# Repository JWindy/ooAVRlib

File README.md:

# ooAVRlib - object oriented AVR library
I started my first embedded projects with Arduino. Due to high power consumption for battery powered projects and relatively large size for projects in confined space, I moved to ATMEL AVR microcontrollers. Mostly, I use ATtiny 85. Since I'm a fan of object oriented programming and I loved the Arduino framework with all the libraries, I started implementing libraries to make life easier. The goal of the libraries is to provide basics functions, to speed up the implementation of new projects. By breaking the functionality down in encapsulated modules, I can reduce complexity for debugging. In case an application source code should get to big, I still can copy the required lines of code together and should have much less troubble interpreting the data sheet and searching for bugs, compared to implementing everything from scratch.
With this repository, I intent to share the libraries to anyone interested and provide some material for beginners, who hopefully have an easier start with my rather simple libraries. It would also be great to find someone willing to contribute to the libraries or get some feedback from more experienced developers. I'm neither a professional software nor hardware engineer;)

# Work in progress
I'm currently working on the initial implementation of the libraries. As soon as the first libraries are tested and ready for use, I'll upload a release.

# How to use the libraries
For every library, you'll find the following folders:
- assets -> any further information like class or block diagrams, if relevant.
- hardware -> This folder contains the design of the hardware used for testing the library. For basic libraries, I'll use a debugging board solderd on a prototype board, which you can find in the folder "debugging boards".
- lib -> If other libraries are required for running the library, the corresponding files are copied here.
- libXX.cpp -> source file
- libXX.h -> header file
- libXXTest.cpp -> test file. The test file shows how to use each function, together with the information in the hardware folder, this should be sufficient documentation to get started:D

# Microcontrollers
For now, the libraries will be implemented for ATtiny 85 running at 8 MHz. I plan on supporting other clock frequencies as well as ATtiny 84 and ATmega 328 in the future.

# Toolchain
I published the project files of the schematics and layouts as well as of the IDE. If you encounter any problems, it might help, to try to open the projects as they are and search for the difference. 
- coding: MPLAB® X IDE -> https://www.microchip.com/en-us/tools-resources/develop/mplab-x-ide
- additional compiler flags: -std=c++14
- programming and debugging: ATMEL-ICE -> https://www.microchip.com/en-us/development-tool/atatmel-ice
- schematics and layouts: KiCad -> https://www.kicad.org/

# Overview over the libraries
The libraries can be grouped in hardware proxies, general purpose libraries, development tools and application level. 
In general, you find more information in the header file of each library, which I don't want to copy here;)
## Hardware Proxies/Drivers
These libraries give access to microcontroller capabilites on the lowest level. Since the ressource can only be accessed by one user, most of the libraries are implemented as singleton and protected by a semaphore.
### libIOHandler
libIOHandler provides basic functions to set a pin as output or input, to activate the internal pullup for input pins, to set a pin high or low and to read the state of a input pin.
### libTimer
This library implements the capabilities of the timer0 and timer1. The timer can be used to trigger interrputs (CTC mode) or to output a PWM signal (PWM mode). 
## General purpose libraries
### libUtility
libUtility contains general type definitions, which will be used to implement the interfaces between libraries. Furthermore, a semaphore is implemented to provide locking functionality especially to hardware proxies to avoide multiple access. This feature might be overengineered for hobby applications, but it was fun to understand, how a semaphore works;)
## Development tools
Development tools are usefull for debugging and testing of other libraries and application code. This group will cover functionality implementing the interface to the serial montior and logging and error handling. The libraries might also be usefull on application level, but so far, I always deactivated these functions, when finishing the project.
### libUartTx
This library provides functions to send strings and numbers (uint and int, 8- and 16-bit) to a serial monitor. To access the UART interface, a USB-UART-adapter is required. I use this function primarily for debugging and logging. libUartTx implements the UART protocol in SW and can be hooked up on any GPIO pin. The library is implemented as singleton, but not protected. So any user can send data. The CPU cycle is blocked until all data is send, so users can access the transmitting function in serial. 
## Application level
So far, I'm still ocupied with the basic libraries;)

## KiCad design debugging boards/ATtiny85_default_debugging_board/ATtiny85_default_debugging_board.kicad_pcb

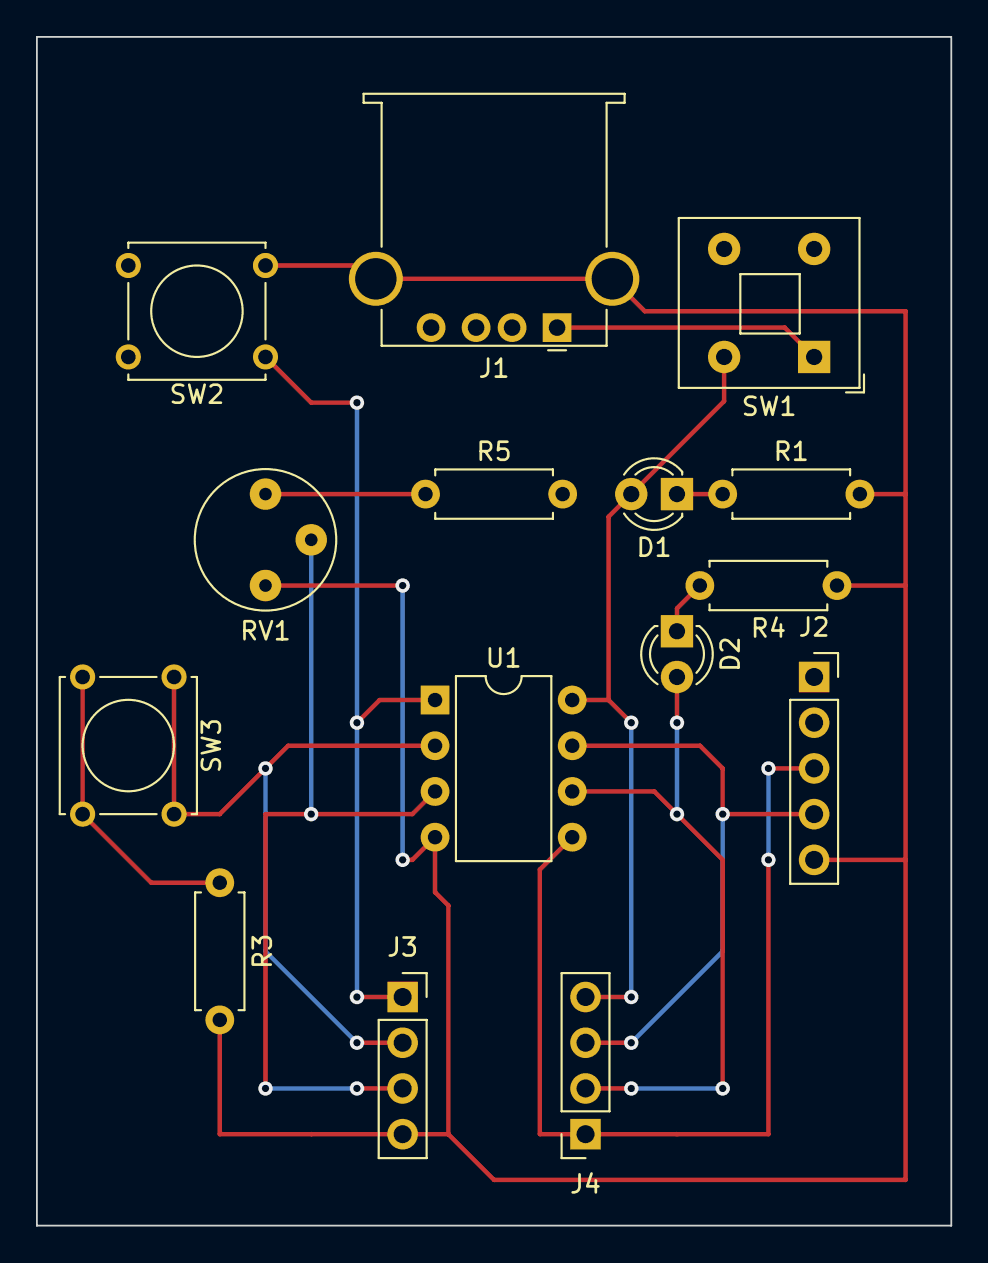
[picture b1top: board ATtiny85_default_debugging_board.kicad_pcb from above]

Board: 2 copper layers, 50.8 x 66.0 mm, 15 parts (0 on the bottom side), 13 nets.

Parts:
D1, D2: LED; LED_D3.0mm
J1: USB_B_Micro; USB_A_Stewart_SS-52100-001_Horizontal
J2: Conn_01x05_Female; PinSocket_1x05_P2.54mm_Vertical
J3, J4: Conn_01x04_Female; PinSocket_1x04_P2.54mm_Vertical
R1, R4: 680; R_Axial_DIN0207_L6.3mm_D2.5mm_P7.62mm_Horizontal
R3: 10 k; R_Axial_DIN0207_L6.3mm_D2.5mm_P7.62mm_Horizontal
R5: 15 k; R_Axial_DIN0207_L6.3mm_D2.5mm_P7.62mm_Horizontal
RV1: 150 k; Potentiometer_Bourns_3339P_Vertical_HandSoldering
SW1: SW_SPST; SW_Push_2P1T_Toggle_CK_PVA1xxH4xxxxxxV2
SW2, SW3: SW_Push; SW_Tactile_Straight_KSA0Axx1LFTR
U1: ATtiny85V-10P; DIP-8_W7.62mm

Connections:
+5V: D1.2 (A), J4.4, R5.2, SW1.2 (B), U1.8 (VCC)
Earth: J1.5 (GND), J2.5, J3.4, R1.2, R3.2, R4.1, RV1.3, SW2.2, U1.4 (GND)
unnamed: D1.1 (K), R1.1
unnamed: D2.1 (K), R4.2
unnamed: J1.1 (VBUS), SW1.1 (A)
unnamed: R3.1, SW3.2
unnamed: R5.1, RV1.1
PB0: J2.3, J4.1, U1.5 (AREF/PB0)
PB1: D2.2 (A), J4.2, U1.6 (PB1)
PB2: J2.4, J4.3, U1.7 (PB2)
PB3: J3.2, SW3.1, U1.2 (XTAL1/PB3)
PB4: J3.3, RV1.2, U1.3 (XTAL2/PB4)
PB5: J3.1, SW2.1, U1.1 (~RESET/PB5)

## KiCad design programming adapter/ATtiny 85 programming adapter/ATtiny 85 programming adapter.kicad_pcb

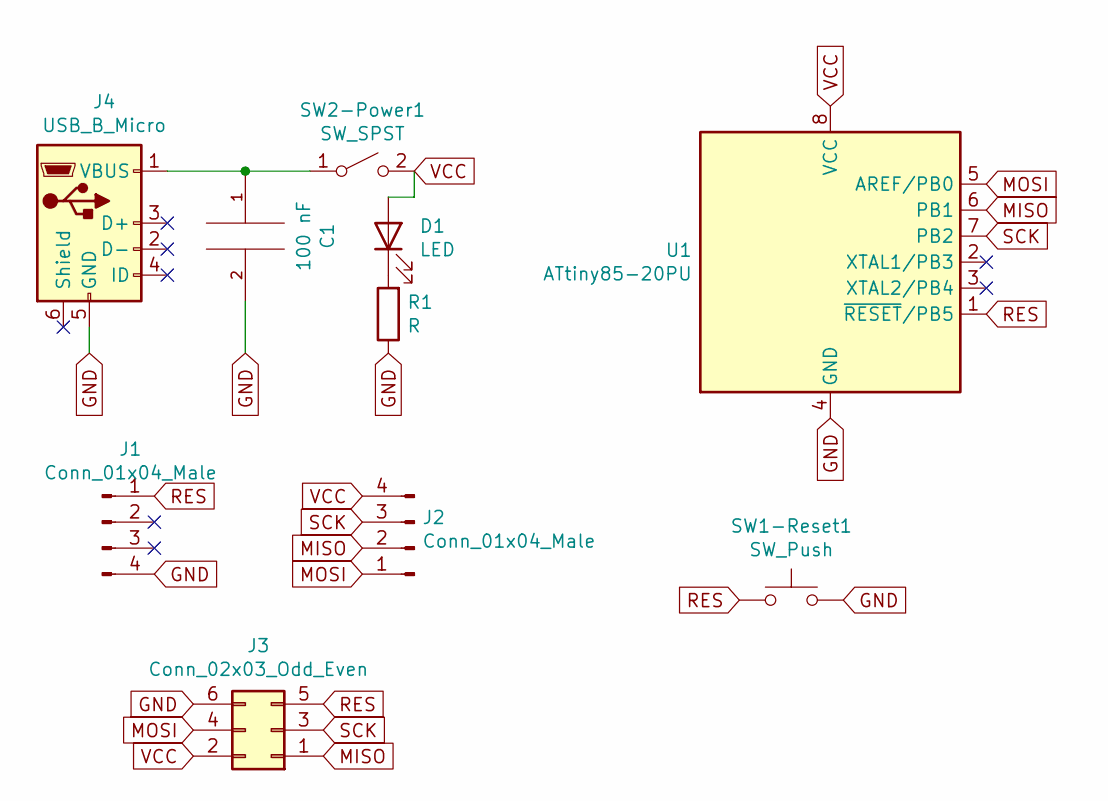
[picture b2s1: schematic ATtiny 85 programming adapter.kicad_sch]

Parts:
C1: 100 nF; C_Axial_L5.1mm_D3.1mm_P7.50mm_Horizontal
D1: LED; LED_D5.0mm
J1, J2: Conn_01x04_Male; PinHeader_1x04_P2.54mm_Vertical
J3: Conn_02x03_Odd_Even; PinHeader_2x03_P2.54mm_Vertical
J4: USB_B_Micro; PinHeader_1x06_P2.54mm_Vertical
R1: R; R_Axial_DIN0207_L6.3mm_D2.5mm_P5.08mm_Vertical
SW1-Reset1: SW_Push; Push_E-Switch_KS01Q01
SW2-Power1: SW_SPST; Push_E-Switch_KS01Q01
U1: ATtiny85-20PU; DIP-8_W7.62mm

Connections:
GND: C1.2, J1.4, J3.6, J4.5 (GND), R1.1, SW1-Reset1.2, U1.4 (GND)
MISO: J2.2, J3.1, U1.6 (PB1)
MOSI: J2.1, J3.4, U1.5 (AREF/PB0)
unnamed: C1.1, J4.1 (VBUS), SW2-Power1.1 (A)
unnamed: D1.1 (K), R1.2
RES: J1.1, J3.5, SW1-Reset1.1, U1.1 (~RESET/PB5)
SCK: J2.3, J3.3, U1.7 (PB2)
VCC: D1.2 (A), J2.4, J3.2, SW2-Power1.2 (B), U1.8 (VCC)

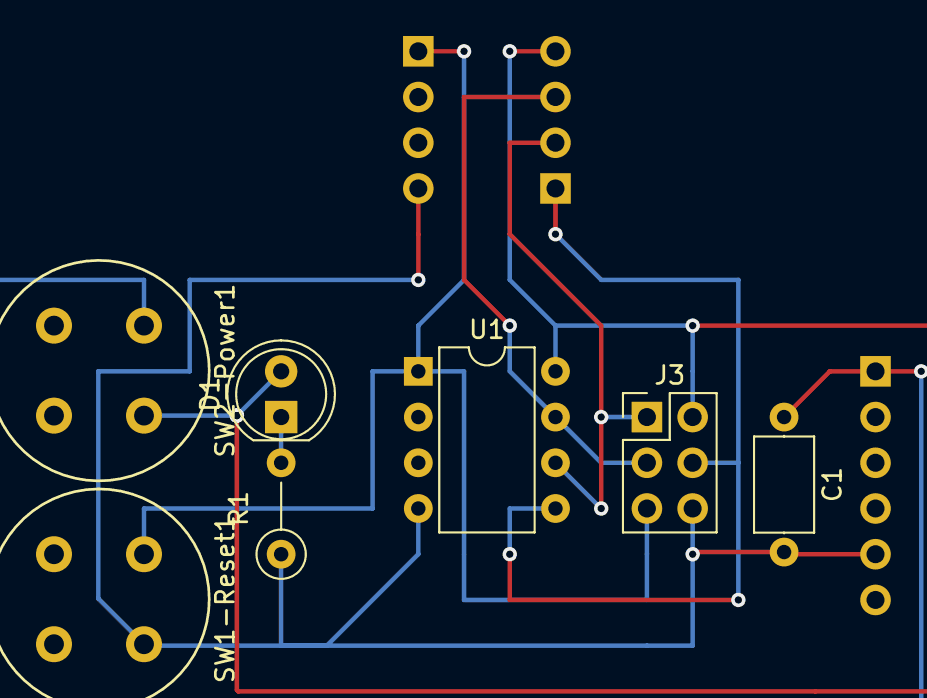
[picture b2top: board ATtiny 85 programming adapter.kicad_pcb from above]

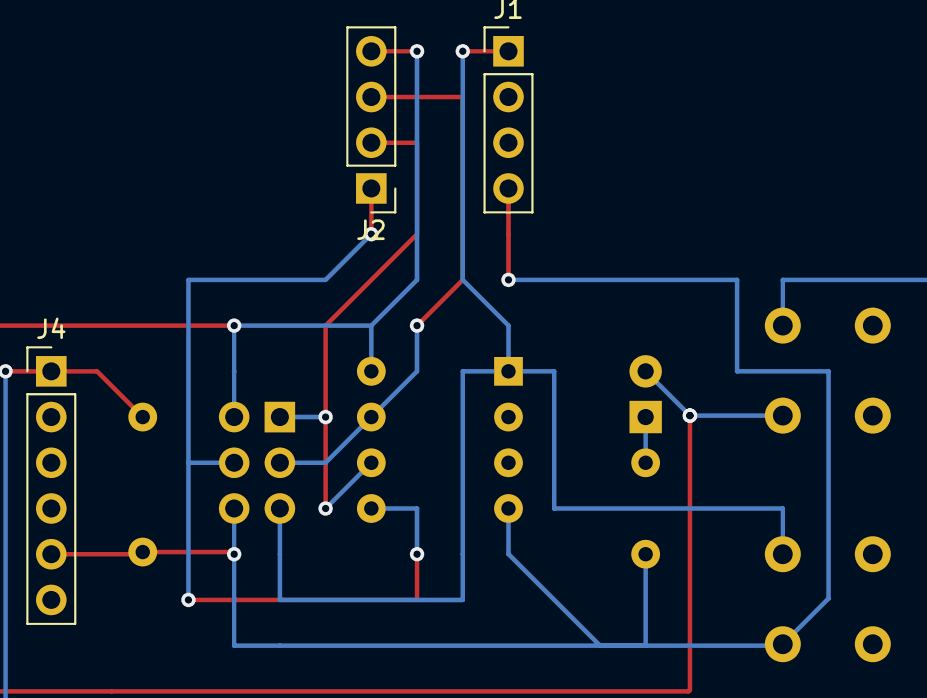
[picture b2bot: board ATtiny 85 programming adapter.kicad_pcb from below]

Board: 2 copper layers, 10 parts (3 on the bottom side), 8 nets.

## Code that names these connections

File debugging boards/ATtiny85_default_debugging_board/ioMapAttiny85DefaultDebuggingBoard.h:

/*--------------------------------------------------------------------
 Description:   Provides the IO mapping for the ATtiny 85 default debugging
                board
  
 Author:        Johannes Windmiller
 
 Dependencies:  none
 
 Version:       v0.1
 
 History:       v0.1     Initial implementation
 
 Supported MUC: ATtiny85
 
 References:
    - Elicia White, Making Embedded Systems, O'Reilly 2012
 
 Copyright:     see LICENSE_software.md in GitHub root folder
 *--------------------------------------------------------------------*/

#ifndef IOMAPATTINY85DEFAULTDEBUGGINGBOARD_H
#define	IOMAPATTINY85DEFAULTDEBUGGINGBOARD_H

#include <avr/io.h>

const uint8_t LED_PIN         = PB1;

const uint8_t BUTTON_PIN      = PB3;

const uint8_t ADC_PIN         = PB4;

const uint8_t UART_Tx_PIN     = PB2;

const uint8_t UART_Rx_PIN     = PB0;

//PB5 reserved for debug wire -> Atmel ICE debugging interface

#endif	/* IOMAPATTINY85DEFAULTDEBUGGINGBOARD_H */

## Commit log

2023-10-16 Rename LICENSE to software_LICENSE.md
2023-10-16 Rename software_LICENSE.md to LICENSE_software.md
2023-10-16 initial creation of README.md
2023-10-16 added .txt to gitignore
2023-10-16 Initial implementation of ATtiny 85 default debugging board for LED, button, UART and ADC test
2023-10-16 Initial implementation of ATtiny 85 programming adapter
2023-10-30 copyright note included, production data exported
2023-10-30 initial implementation started
2023-10-30 irrelevant files deleted
2023-10-30 UART 2 USB 4x1 socket turned by 180°, some traces rerouted -> simpler layout
2023-10-31 asdf
2023-10-31 pictures added ATtiny 85 programming and debugging boards
2023-10-31 libIoHandler renamed to libIOHandler
2023-10-31 libIOHandler set and write to output, set and read input implemented and tested
2023-10-31 Minor update libIOHandler
2023-10-31 initial implementation
2023-10-31 template for source and header file applied, libIOHandler copied
2023-11-01 Minor update
2023-11-03 initial implementation -> struct for versioning of classes
2023-11-03 versioning of class implemented
2023-11-03 Header of header extended by comment and dependencies, versioning of class implemented
2023-11-03 Versioning of dependenca of libIOHandler to libUtility updated
2023-11-03 Spelling of project name corrected
2023-11-03 Correction of spelling mistake
2023-11-03 Initial implementation of libUtility
2023-11-03 Some update in a project xml file
2023-11-06 Initial implementation, first working version, WIP
2023-11-06 status_t added
2023-11-06 Stable version, printStr, printLn, printNum(uintX_t), printNum(intX), printBinary implemented
2023-11-07 Template implemented for printing singned and unsigned integers (stable)
2023-11-07 Tuning algorithm for timer interrupt compare value implemented (stable)
2023-11-07 Removed argument for timer compar interrupt to constructor
2023-11-08 Class converted to singleton (stable)
2023-11-15 dynamic allocation of Singleton changed to static allocation (stable)
2023-11-15 Initial implementation, no compiling errors (WIP)
2023-11-16 Naming of status_t change to uppercase (const...), Semaphore implemented (stable)
    ToDo: move test case from libTimerTest to libUtilityTest
2023-11-16 ioMapAttiny85DefaultDebuggingBoard updated to correct pins
2023-11-16 Timer tests implemented. Tests passed. (stable)
    ToDo: implement PWM tests, move semaphore test zu libUtility
2023-11-16 Dependency to libUtility updated from v0.1 to v0.2
    has no impact on libUtility...
2023-11-16 Update of available libraries
2023-11-18 Overflow interrupt implemented, PWM test and overflow tests implemented and passed. timer 0 implementation done. (stable)
2023-11-19 toggleLED() change to binary xorg (stable)
2023-11-19 Test case for semaphor implemented and passed (stable)
2023-11-19 ATtiny85 LED debugging board created
2023-11-19 Timer1 implemented, tests passed, ioHandler for LED debugging board included (stable)
2023-11-20 Calculation spread sheet for prescaler and compare match value extended for timer1
2023-11-20 Program memory required per function call of semaphore added
2023-11-20 Define of microcontroller flag removed - should be set in IDE
2023-11-21 Test cases organized in switch case, some bugs fixed, test of prescalers and timer1 change OCR1C implemented (stable)
2023-11-21 Compare macht OCRxB implemented and tested for timer0 and timer1 (stable)
2023-12-11 READY_STATE added
2023-12-18 Change Ctor to explicit
2023-12-18 Correct error (#elif to #else)
2023-12-18 Polymorphic class changed to template implementation (WIP)
2023-12-18 Max number of users for semaphore passed by initialisation() (stable)
    all tests passed
2023-12-21 Change class name from libIOHandler to IOHandler
2023-12-21 non-class member instansiateObject() replaced
    non-class member instansiateObject() included in class-member initialise()
2023-12-21 Singleton template implemented
2023-12-21 libTimer included - partially tested -> partial stable :D (WIP)
2024-01-07 Switch case in printNum replaced by if, to enable compiler optimization
